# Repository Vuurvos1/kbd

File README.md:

<div align="center">
    <center>
        
    </center>
</div>

<div align="center">
    <center>
        <h1 align="center"><b>KBD</b></h1>
    </center>
    <center>
        <p align="center">Custom keyboards and key maps</p>
    </center>
</div>

## Projects

- [**KBD1**](kbd1/) — A 56-key split wireless keyboard inspired by the Corne and Lily58, designed with Ergogen and KiCad. See the [KBD1 README](kbd1/README.md) for the full BOM.
- **Dactyl CC** — Custom keymaps for the Dactyl CC keyboard (QMK), including a [Vial](keyboards/dactyl_cc/readme.md#vial--remapping-in-the-browser) keymap for remapping in the browser
- **Footprints** — Reusable KiCad footprints for hotswap sockets, panelization, and more

## Requirements

- [KiCad](https://www.kicad.org/) - PCB design
- [Ergogen](https://docs.ergogen.xyz/) - Procedural keyboard layout generator
- [pnpm](https://pnpm.io/installation) - Package manager

## Credits

- https://github.com/ai03-2725/MX_V2 - Keyboard switch footprints and models
- https://github.com/christianselig/caldera-keyboard - Keyboard design
- https://github.com/modern-hobbyist/aesir - Keyboard design and inspiration for merged hotswap footprints
- https://github.com/madworm/Panelization.pretty - Mouse-bite panelization footprints

## License

This project is licensed under the [MIT License](LICENSE).

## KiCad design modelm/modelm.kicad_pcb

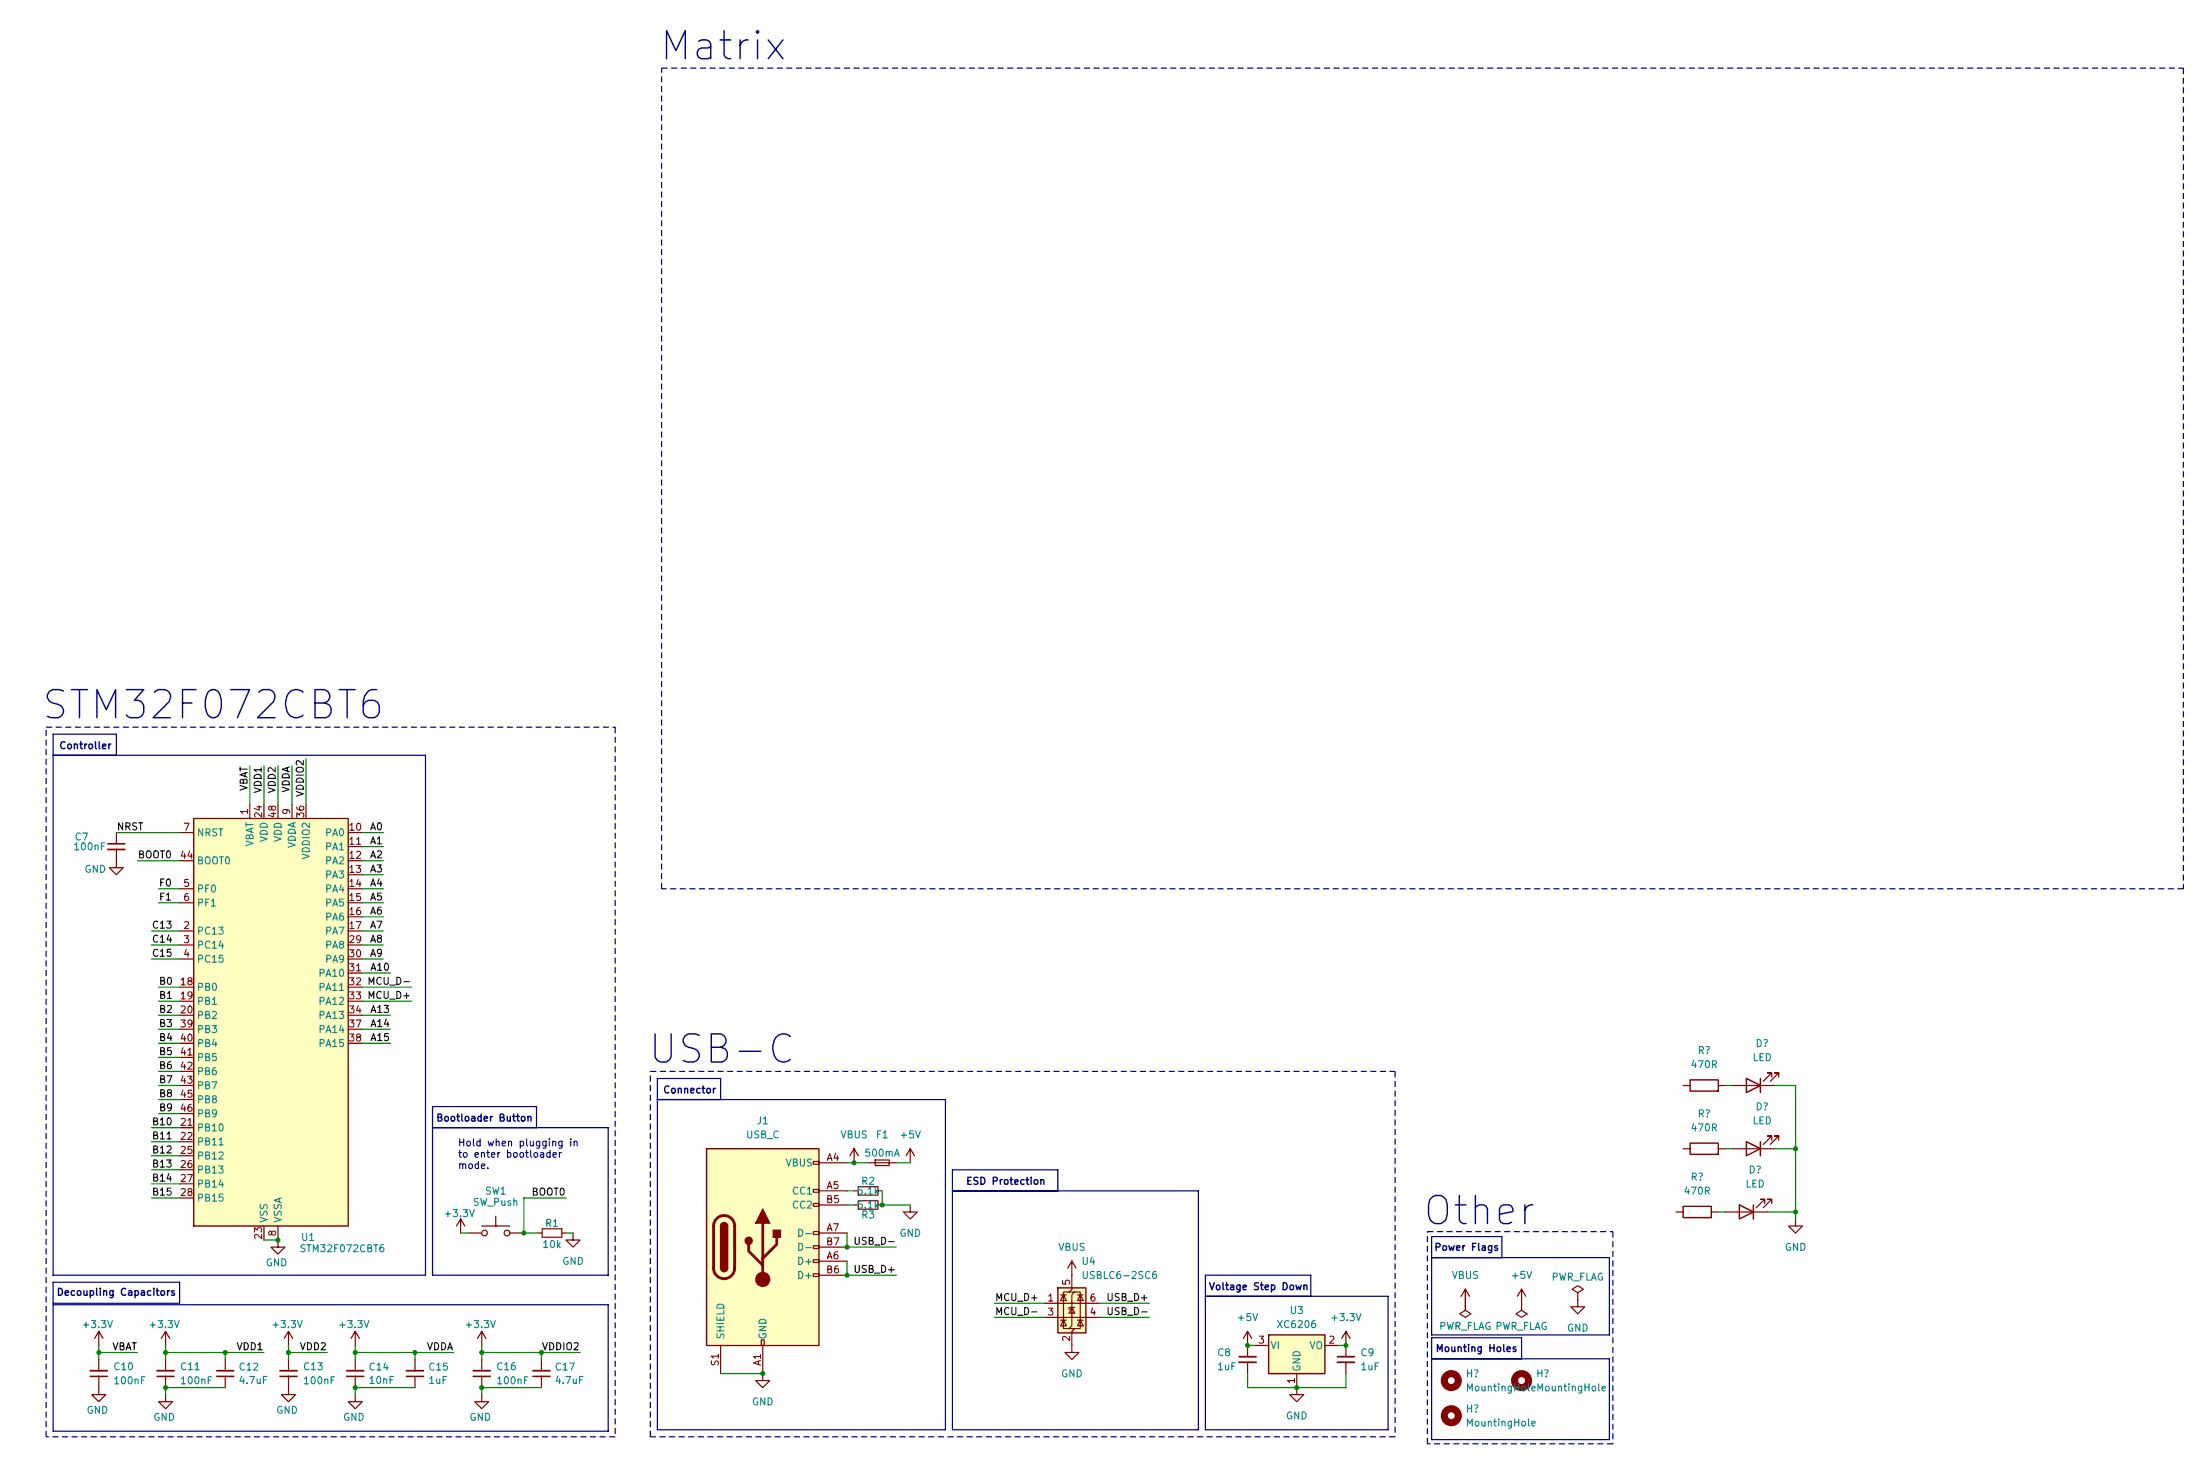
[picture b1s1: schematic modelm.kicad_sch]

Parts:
C7: 100nF; Capacitor_0402; LCSC C307331
C8, C9: 1uF; Capacitor_0402; LCSC C52923
C10, C11, C13, C16: 100nF; Capacitor_0402; MPN CL05B104KB54PNC; LCSC C307331
C12, C17: 4.7uF; Capacitor_0402; MPN CL05A475MP5NRNC; LCSC C23733
C14: 10nF; Capacitor_0402; MPN CL05B103KB5NNNC; LCSC C15195
C15: 1uF; Capacitor_0402; MPN CL05A105KA5NQNC; LCSC C52923
F1: 500mA; Fuse_0603; LCSC C210357
J1: USB_C; USB_C_HRO_TYPE-C-31-M-12; LCSC C165948
R1: 10k; Resistor_0402; LCSC C25744
R2, R3: 5.1k; Resistor_0402; LCSC C25905
SW1: SW_Push; Button_TL3342; LCSC C115351
U1: STM32F072CBT6; Package_LQFP-48_7x7mm_P0.5; LCSC C81720
U3: XC6206; Voltage_SOT-23; LCSC C5446
U4: USBLC6-2SC6; ESD_SOT-23-6; LCSC C2827654

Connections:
+3.3V: C9.1, C10.2, C11.2, C12.2, C13.2, C14.2, C15.2, C16.2, C17.2, SW1.1, U1.1 (VBAT), U1.9 (VDDA), U1.24 (VDD), U1.36 (VDDIO2), U1.48 (VDD), U3.2 (VO)
+5V: C8.1, F1.2, U3.3 (VI)
/A0: U1.10 (PA0)
/A1: U1.11 (PA1)
/A2: U1.12 (PA2)
/A3: U1.13 (PA3)
/A4: U1.14 (PA4)
/A5: U1.15 (PA5)
/A6: U1.16 (PA6)
/A7: U1.17 (PA7)
/A8: U1.29 (PA8)
/A9: U1.30 (PA9)
/A10: U1.31 (PA10)
/A13: U1.34 (PA13)
/A14: U1.37 (PA14)
/A15: U1.38 (PA15)
/B0: U1.18 (PB0)
/B1: U1.19 (PB1)
/B2: U1.20 (PB2)
/B3: U1.39 (PB3)
/B4: U1.40 (PB4)
/B5: U1.41 (PB5)
/B6: U1.42 (PB6)
/B7: U1.43 (PB7)
/B8: U1.45 (PB8)
/B9: U1.46 (PB9)
/B10: U1.21 (PB10)
/B11: U1.22 (PB11)
/B12: U1.25 (PB12)
/B13: U1.26 (PB13)
/B14: U1.27 (PB14)
/B15: U1.28 (PB15)
/BOOT0: R1.2, SW1.2, U1.44 (BOOT0)
/C13: U1.2 (PC13)
/C14: U1.3 (PC14)
/C15: U1.4 (PC15)
/F0: U1.5 (PF0)
/F1: U1.6 (PF1)
/MCU_D+: U1.33 (PA12), U4.1 (I/O1)
/MCU_D-: U1.32 (PA11), U4.3 (I/O2)
/NRST: C7.1, U1.7 (NRST)
/USB_D+: J1.A6 (D+), J1.B6 (D+), U4.6 (I/O1)
/USB_D-: J1.A7 (D-), J1.B7 (D-), U4.4 (I/O2)
GND: C7.2, C8.2, C9.2, C10.1, C11.1, C12.1, C13.1, C14.1, C15.1, C16.1, C17.1, J1.A1 (GND), J1.A12 (GND), J1.B1 (GND), J1.B12 (GND), J1.S1 (SHIELD), R1.1, R2.2, R3.2, U1.8 (VSSA), U1.23 (VSS), U1.35 (VSS), U1.47 (VSS), U3.1 (GND), U4.2 (GND)
unnamed: J1.A5 (CC1), R2.1
unnamed: J1.B5 (CC2), R3.1
VBUS: F1.1, J1.A4 (VBUS), J1.A9 (VBUS), J1.B4 (VBUS), J1.B9 (VBUS), U4.5 (VBUS)

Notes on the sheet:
STM32F072CBT6
USB-C
Mounting Holes
Decoupling Capacitors
Controller
ESD Protection
Power Flags
Voltage Step Down
Other
Bootloader Button
Matrix
Connector
Hold when plugging in to enter bootloader mode.

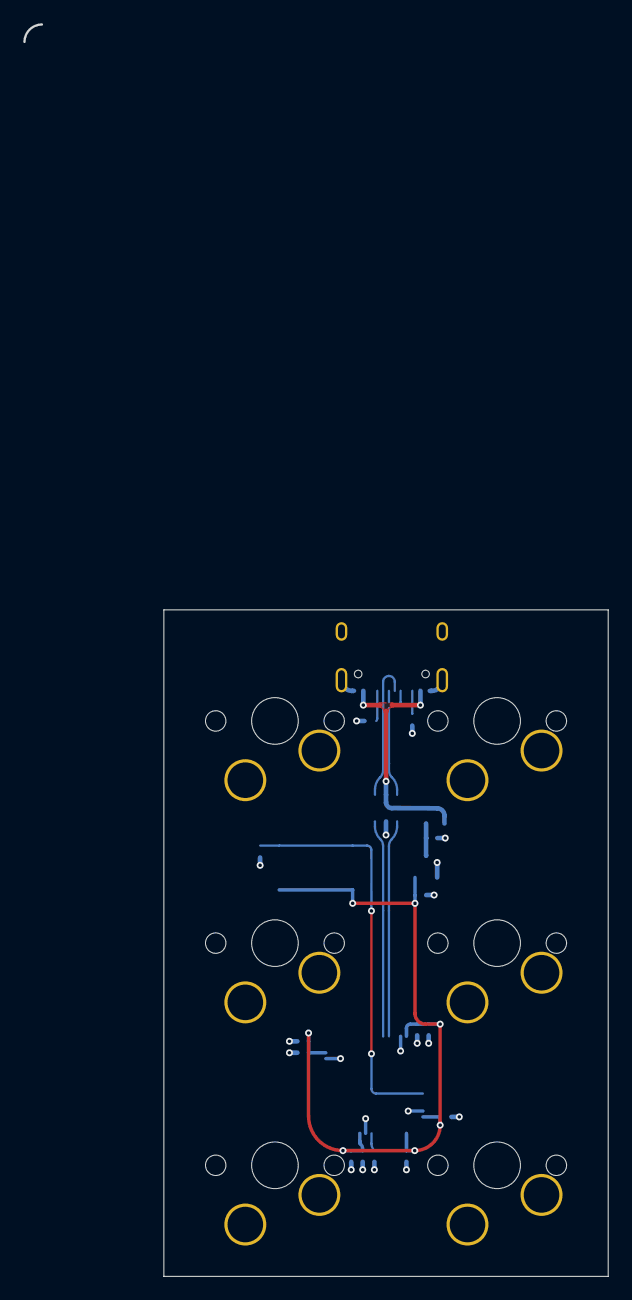
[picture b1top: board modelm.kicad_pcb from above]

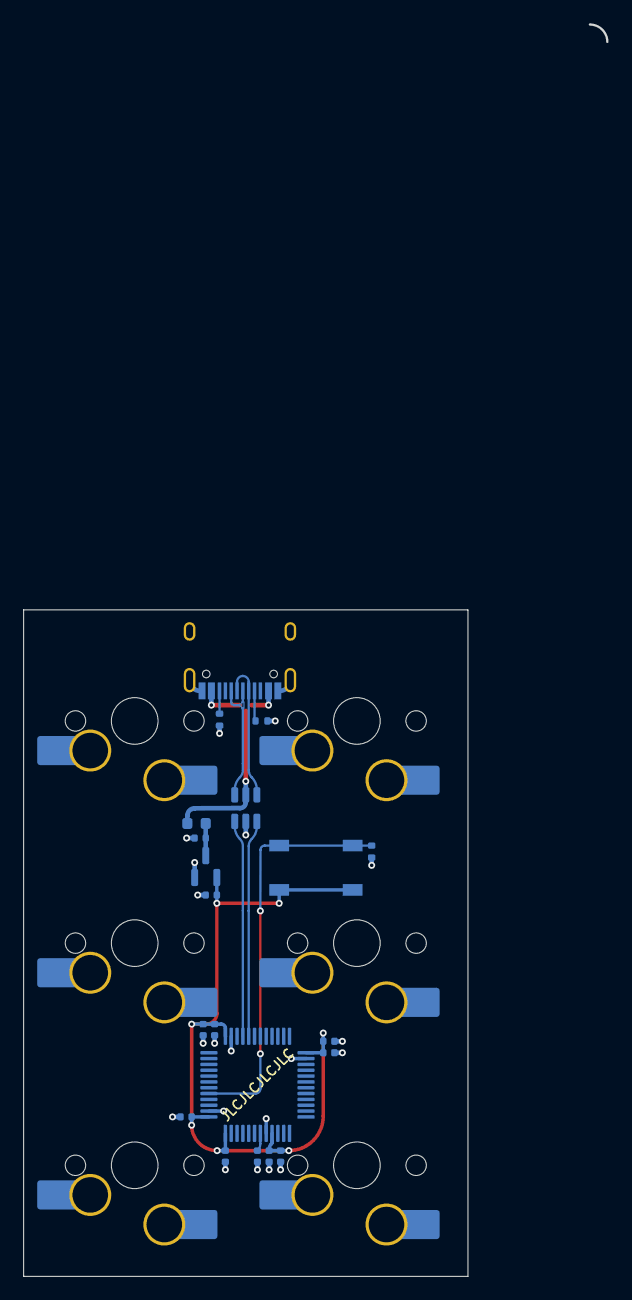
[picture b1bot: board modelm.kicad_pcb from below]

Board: 4 copper layers, 38.1 x 57.2 mm, 20 parts (20 on the bottom side), 12 nets.

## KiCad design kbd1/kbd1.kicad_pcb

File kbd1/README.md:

# KBD1

A Corne / Lily58 inspired 56-key split wireless keyboard, designed with [Ergogen](https://docs.ergogen.xyz/) and [KiCad](https://www.kicad.org/).

## BOM (Bill of Materials)

For a full build you need:

| Qty | Component               | Notes                                                      |
| --- | ----------------------- | ---------------------------------------------------------- |
| 56x | KS-33 hotswap sockets   | or MX hotswap sockets                                      |
| 56x | KS-33 switches          | or MX style switches                                       |
| 56x | SOD-123 diodes          |                                                            |
| 2x  | Panasonic EVQPUC        | reset button                                               |
| 2x  | PCM12SMTR               | power switch (or Alps SSSS811101 / G-Switch MK-12C02-G015) |
| 2x  | JST PH 2-pin (2.0mm)    | for battery connection                                     |
| 2x  | 3.7V 750mAh LiPo       | ~35x50x3.5mm                                               |
| 2x  | nice!nano v2            | or compatible nRF52840 board                               |
| 4x  | Mill-Max 1x12 sockets   | for socketing the MCUs                                     |
| —   | MCU pins                | diode legs work well                                       |
| 4x  | M2.5x3x3.5 heatset inserts | for case assembly                                      |
| 6x  | M2.5x4x3.5 heatset inserts | for case assembly                                      |
| 4x  | M2.5x6 countersunk screws  | for case assembly                                      |
| 6x  | M2.5x8 countersunk screws  | for case assembly                                      |
| 8x  | Rubber feet             | 10mm circle                                                |
| 1x  | Keycap set              | LSA or similar                                             |
| 2x  | nice!view display       | optional                                                   |

## Firmware

This keyboard runs [ZMK](https://zmk.dev/) firmware. The keymap and configuration are in the [`config/`](../config/) directory.

Firmware is automatically built by GitHub Actions on every push. Download the latest `.uf2` files from the [Actions](../../actions) tab, then flash by double-tapping the reset button and copying the file to the USB drive that appears.

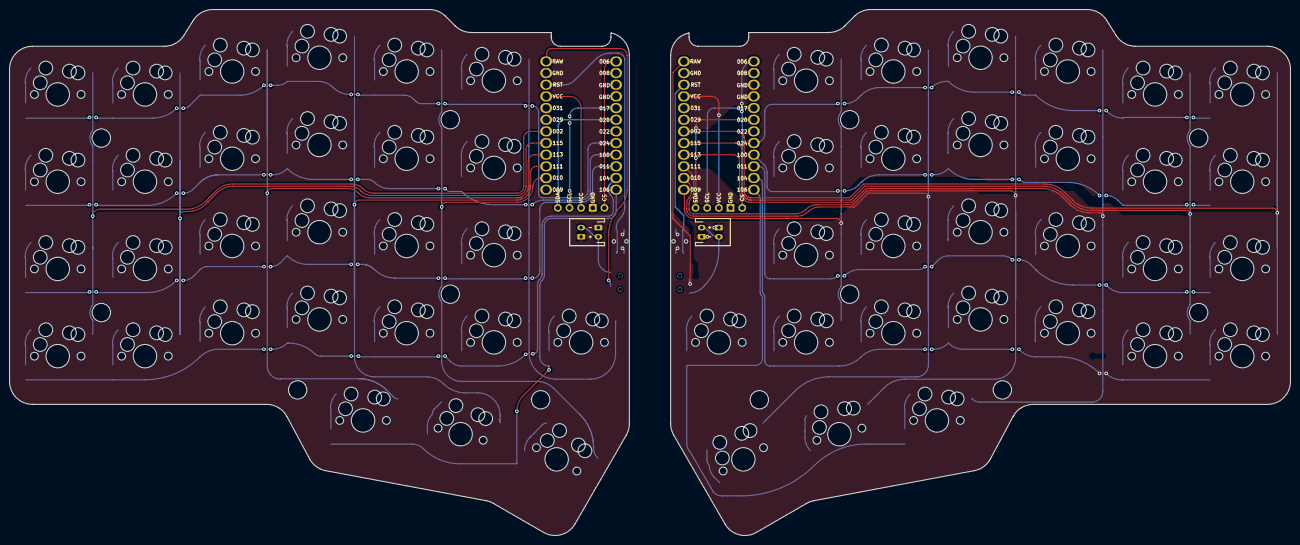
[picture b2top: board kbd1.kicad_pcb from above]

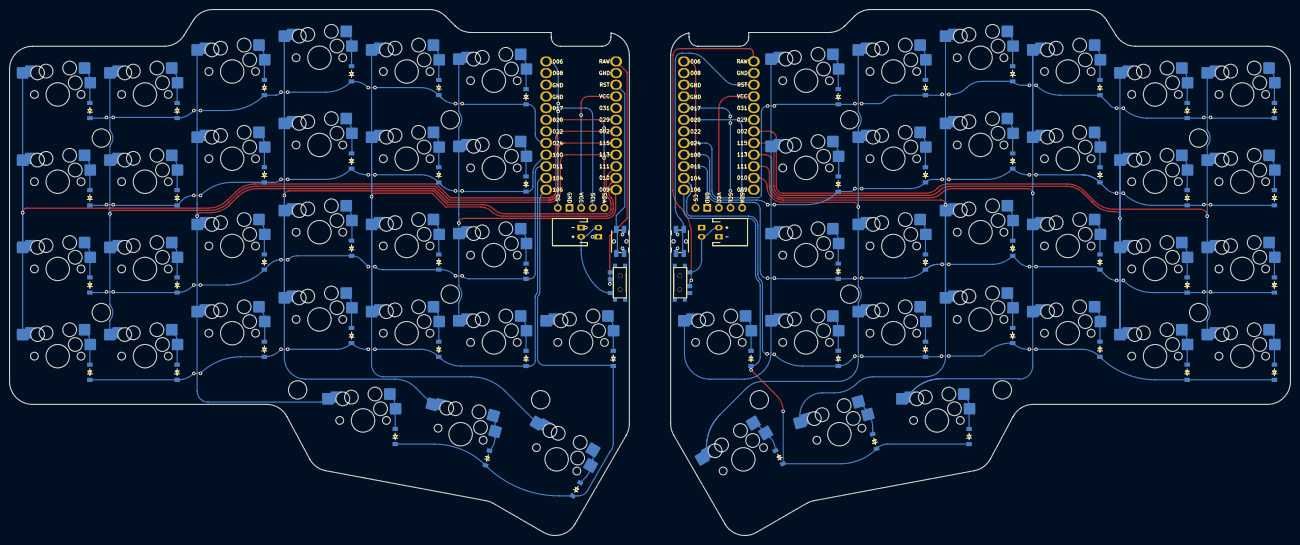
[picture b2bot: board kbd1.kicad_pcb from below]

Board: 2 copper layers, 279.0 x 114.6 mm, 124 parts (2 on the bottom side), 79 nets.

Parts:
B1, B2: Panasonic_EVQPUL_EVQPUC
D1, D2, D3, D4, D5, D6, D7, D8, D9, D10, D11, D12, D13, D14, D15, D16, D17, D18, D19, D20, D21, D22, D23, D24, D25, D26, D27, D28, D29, D30, D31, D32, D33, D34, D35, D36, D37, D38, D39, D40, D41, D42, D43, D44, D45, D46, D47, D48, D49, D50, D51, D52, D53, D54, D55, D56: ComboDiode
JST1, JST2, JST3, JST4: JST_PH_S2B-PH-K_02x2.00mm_Angled
MCU1, MCU2: nice_nano_low_profile
S1, S2, S3, S4, S5, S6, S7, S8, S9, S10, S11, S12, S13, S14, S15, S16, S17, S18, S19, S20, S21, S22, S23, S24, S25, S26, S27, S28, S29, S30, S31, S32, S33, S34, S35, S36, S37, S38, S39, S40, S41, S42, S43, S44, S45, S46, S47, S48, S49, S50, S51, S52, S53, S54, S55, S56: KS33-MX-Hotswap
T1, T2: SPDT_C128955
niceView1, niceView2: niceView; niceView_headers

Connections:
GND: B1.1, B2.1, JST1.1, JST2.2, JST3.1, JST4.2, MCU1.2, MCU1.15, MCU1.16, MCU2.2, MCU2.15, MCU2.16, niceView1.2, niceView2.2
P002: MCU1.7, MCU2.7, S1.1, S2.1, S3.1, S4.1, S29.1, S30.1, S31.1, S32.1
P006: MCU1.13, MCU2.13, niceView1.1, niceView2.1
P008: MCU1.14, MCU2.14
P009: MCU1.12, MCU2.12, S21.1, S22.1, S23.1, S24.1, S28.1, S49.1, S50.1, S51.1, S52.1, S56.1
P010: MCU1.11, MCU2.11, S17.1, S18.1, S19.1, S20.1, S27.1, S45.1, S46.1, S47.1, S48.1, S55.1
P011: D2.1, D6.1, D10.1, D14.1, D18.1, D22.1, D30.1, D34.1, D38.1, D42.1, D46.1, D50.1, MCU1.22, MCU2.22
P017: MCU1.17, MCU2.17, niceView1.4, niceView2.4
P020: MCU1.18, MCU2.18, niceView1.5, niceView2.5
P022: MCU1.19, MCU2.19
P024: D4.1, D8.1, D12.1, D16.1, D20.1, D24.1, D32.1, D36.1, D40.1, D44.1, D48.1, D52.1, MCU1.20, MCU2.20
P029: MCU1.6, MCU2.6
P031: MCU1.5, MCU2.5
P100: D3.1, D7.1, D11.1, D15.1, D19.1, D23.1, D31.1, D35.1, D39.1, D43.1, D47.1, D51.1, MCU1.21, MCU2.21
P104: D1.1, D5.1, D9.1, D13.1, D17.1, D21.1, D29.1, D33.1, D37.1, D41.1, D45.1, D49.1, MCU1.23, MCU2.23
P106: D25.1, D26.1, D27.1, D28.1, D53.1, D54.1, D55.1, D56.1, MCU1.24, MCU2.24
P111: MCU1.10, MCU2.10, S13.1, S14.1, S15.1, S16.1, S26.1, S41.1, S42.1, S43.1, S44.1, S54.1
P113: MCU1.9, MCU2.9, S9.1, S10.1, S11.1, S12.1, S25.1, S37.1, S38.1, S39.1, S40.1, S53.1
P115: MCU1.8, MCU2.8, S5.1, S6.1, S7.1, S8.1, S33.1, S34.1, S35.1, S36.1
RAW: MCU1.1, MCU2.1, T1.2, T2.2
RST: B1.2, B2.2, MCU1.3, MCU2.3
VCC: MCU1.4, MCU2.4, niceView1.3, niceView2.3
far_thumb: D27.2, S27.2
home_thumb: D26.2, S26.2
index_bottom: D18.2, S18.2
index_home: D19.2, S19.2
index_mod: D17.2, S17.2
index_top: D20.2, S20.2
inner_bottom: D22.2, S22.2
inner_home: D23.2, S23.2
inner_mod: D21.2, S21.2
inner_top: D24.2, S24.2
middle_bottom: D14.2, S14.2
middle_home: D15.2, S15.2
middle_mod: D13.2, S13.2
middle_top: D16.2, S16.2
mirror_far_thumb: D55.2, S55.2
mirror_home_thumb: D54.2, S54.2
mirror_index_bottom: D46.2, S46.2
mirror_index_home: D47.2, S47.2
mirror_index_mod: D45.2, S45.2
mirror_index_top: D48.2, S48.2
mirror_inner_bottom: D50.2, S50.2
mirror_inner_home: D51.2, S51.2
mirror_inner_mod: D49.2, S49.2
mirror_inner_top: D52.2, S52.2
mirror_middle_bottom: D42.2, S42.2
mirror_middle_home: D43.2, S43.2
mirror_middle_mod: D41.2, S41.2
mirror_middle_top: D44.2, S44.2
mirror_near_thumb: D53.2, S53.2
mirror_outer_bottom: D30.2, S30.2
mirror_outer_home: D31.2, S31.2
mirror_outer_mod: D29.2, S29.2
mirror_outer_top: D32.2, S32.2
mirror_pinky_bottom: D34.2, S34.2
mirror_pinky_home: D35.2, S35.2
mirror_pinky_mod: D33.2, S33.2
mirror_pinky_top: D36.2, S36.2
mirror_ring_bottom: D38.2, S38.2
mirror_ring_home: D39.2, S39.2
mirror_ring_mod: D37.2, S37.2
mirror_ring_top: D40.2, S40.2
mirror_top_thumb: D56.2, S56.2
near_thumb: D25.2, S25.2
outer_bottom: D2.2, S2.2
outer_home: D3.2, S3.2
outer_mod: D1.2, S1.2
outer_top: D4.2, S4.2
pinky_bottom: D6.2, S6.2
pinky_home: D7.2, S7.2
pinky_mod: D5.2, S5.2
pinky_top: D8.2, S8.2
pos: JST1.2, JST2.1, JST3.2, JST4.1, T1.1, T2.1
ring_bottom: D10.2, S10.2
ring_home: D11.2, S11.2
ring_mod: D9.2, S9.2
ring_top: D12.2, S12.2
top_thumb: D28.2, S28.2

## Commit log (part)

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2025-02-21 add kbd1 config and footprints
2025-02-23 outline and pcb updates
2025-02-26 file watching and mounting holes
2025-02-26 assigning row and col nets
2025-03-03 tweaking layout and pins
2025-04-01 add dactyl keymap
2025-08-15 stuff
2026-02-05 tweak key positions
2026-02-05 fix watch
2026-02-05 tweak position
2026-02-05 tweak outline
2026-02-06 outline tweaking
2026-02-06 feat: stl gen
2026-02-09 custom footprints and layout tweaking
2026-02-09 footprint tweaking
2026-02-10 fix: interferance issues
2026-02-11 create merged hotswap socket
2026-02-11 feat: add right board outline
2026-02-12 better right spacing
2026-02-12 fix: usb port alignment
2026-02-12 tweak mcu placement and footprint
2026-02-12 docs
2026-02-13 mirror electronics
2026-02-13 add holes back
2026-02-13 add credits
2026-02-19 flip jst
2026-04-01 fix angle
2026-04-04 tweak angles
2026-04-06 tweak diode positioning
2026-04-06 mirroring parts
2026-04-07 moving and mirroring more parts
2026-04-07 tweak footprints
2026-04-07 kbd1 pcb
2026-04-08 wip: panelization
2026-04-08 feat: panelizing and refining
2026-04-10 init zmk
2026-04-10 update kbd
2026-04-10 zmk files
2026-04-19 fix: zmk
2026-04-19 fix: pinout
2026-04-19 tweak keymap
2026-04-19 enable zmk studio
2026-04-19 fix ci
2026-04-20 flip right columns
2026-04-25 setup qmk userspace
2026-04-25 move jst connector
2026-04-29 add model m pcbs
2026-04-29 Add MIT License to the project
2026-04-29 update readmes
2026-04-29 update pcb
2026-04-29 add case files
2026-04-29 update bom
2026-04-29 add gerber zip
2026-04-29 add firmware note
2026-04-29 add keyboard image
